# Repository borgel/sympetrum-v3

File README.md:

# What?
An electronic conference badge, of course! (That makes this a wearable right?)

If you're interested in keeping up to date with new versions, you can add your email here: 
https://goo.gl/forms/xGFPdRpdT4x1kmzG3 I'll send out (few) updates as I make progress towards whatever the next version is.

## Yes, but what does it do?
By default the device does pleasant RGB fades across its 48 RGB LEDs. It also sends a beacon in infrared every 30 seconds. They use any beacons received to synchronize a clock from which an animation is derived. The effect is that if one is alone, it plays random colors. If a group of them are together, they play the same rainbow water drop animation together.

For a little more information, last year's was [written up by Hackaday here](https://hackaday.com/2017/07/14/badge-from-diamond-age-comes-to-def-con/).

This is a partial rewrite of the work done for [DEFCON](https://defcon.org/) 25 ([here](https://github.com/borgel/sympetrum-v2)).

## Why is it a dragonfly?
If you haven't read Neal Stephenson's [_The Diamond Age: or, A Young Lady's Illustrated Primer_](http://www.goodreads.com/book/show/827.The_Diamond_Age), do that first. I'll wait.

If you have, there's a sequence around page 300 in which Miranda is first introduced to the possibility of using the drummers to find Nell. In this scene she attends a party in which the revellers wear colorful cloisonné dragonfly pins. As the party progresses they transition from random colorful flickering to some sort of synchrony, and Miranda notices the participants do the same. This is what I built.

A [_Sympetrum_](https://en.wikipedia.org/wiki/Sympetrum) is a genus of Dragonfly.

# Addons
Assembly instructions here: https://docs.google.com/document/d/1MZ-Gf56ivJ_pZaOBdA2XsJtWuKzQMPqqDXrGzq-pdRY/edit?usp=sharing

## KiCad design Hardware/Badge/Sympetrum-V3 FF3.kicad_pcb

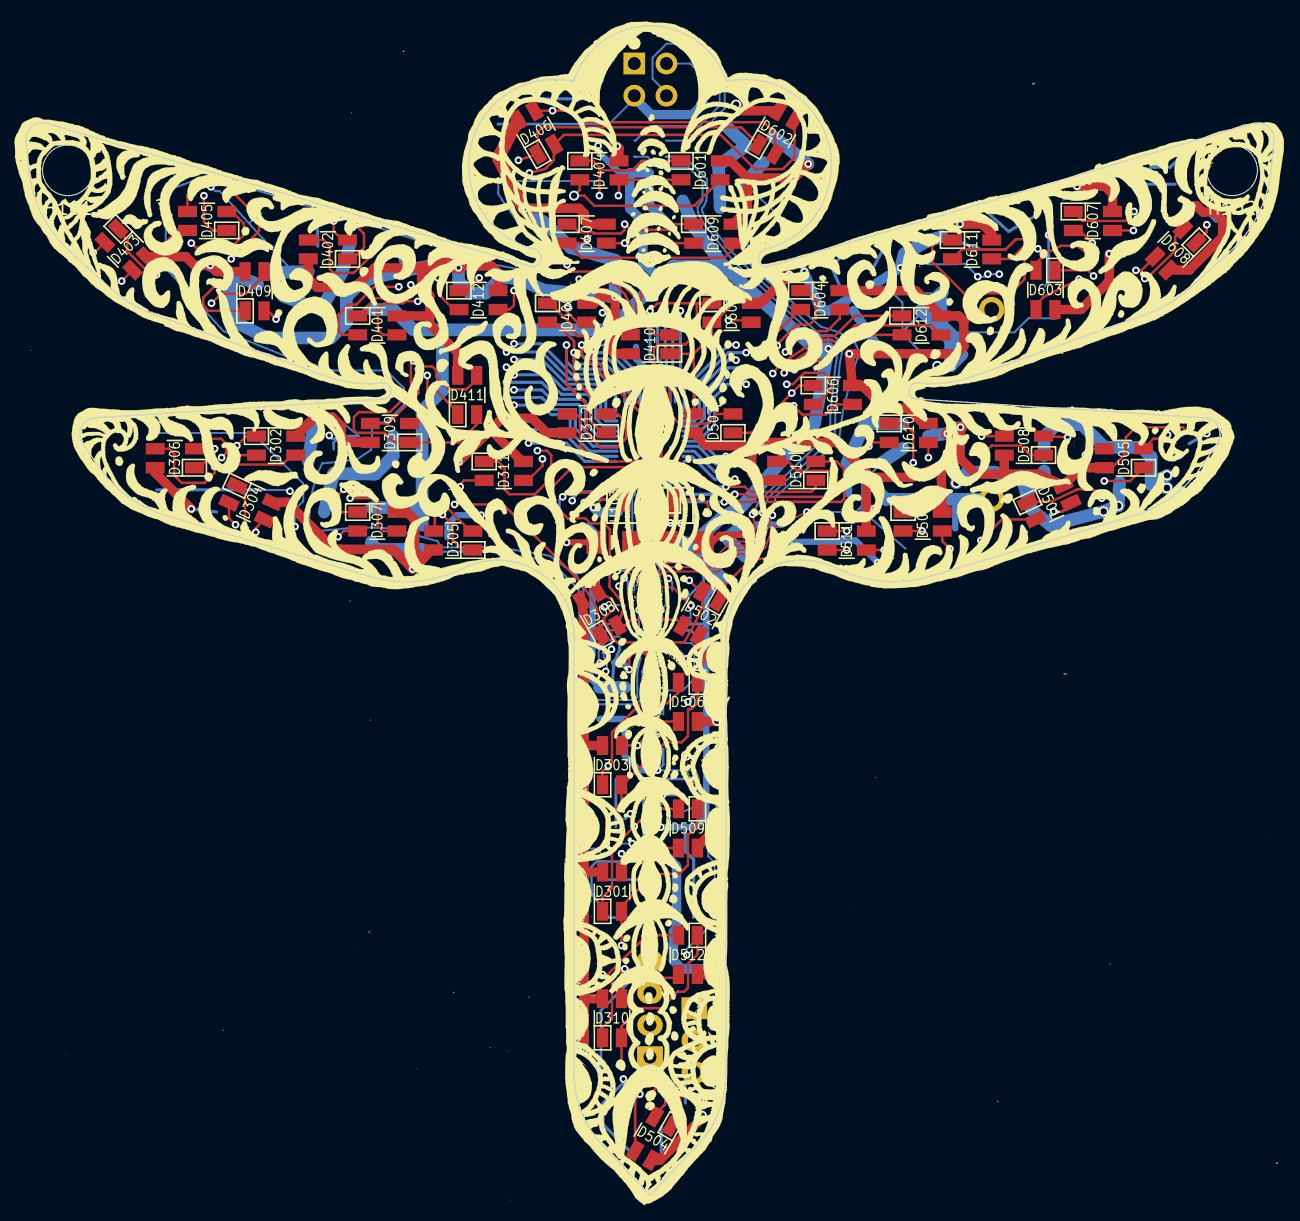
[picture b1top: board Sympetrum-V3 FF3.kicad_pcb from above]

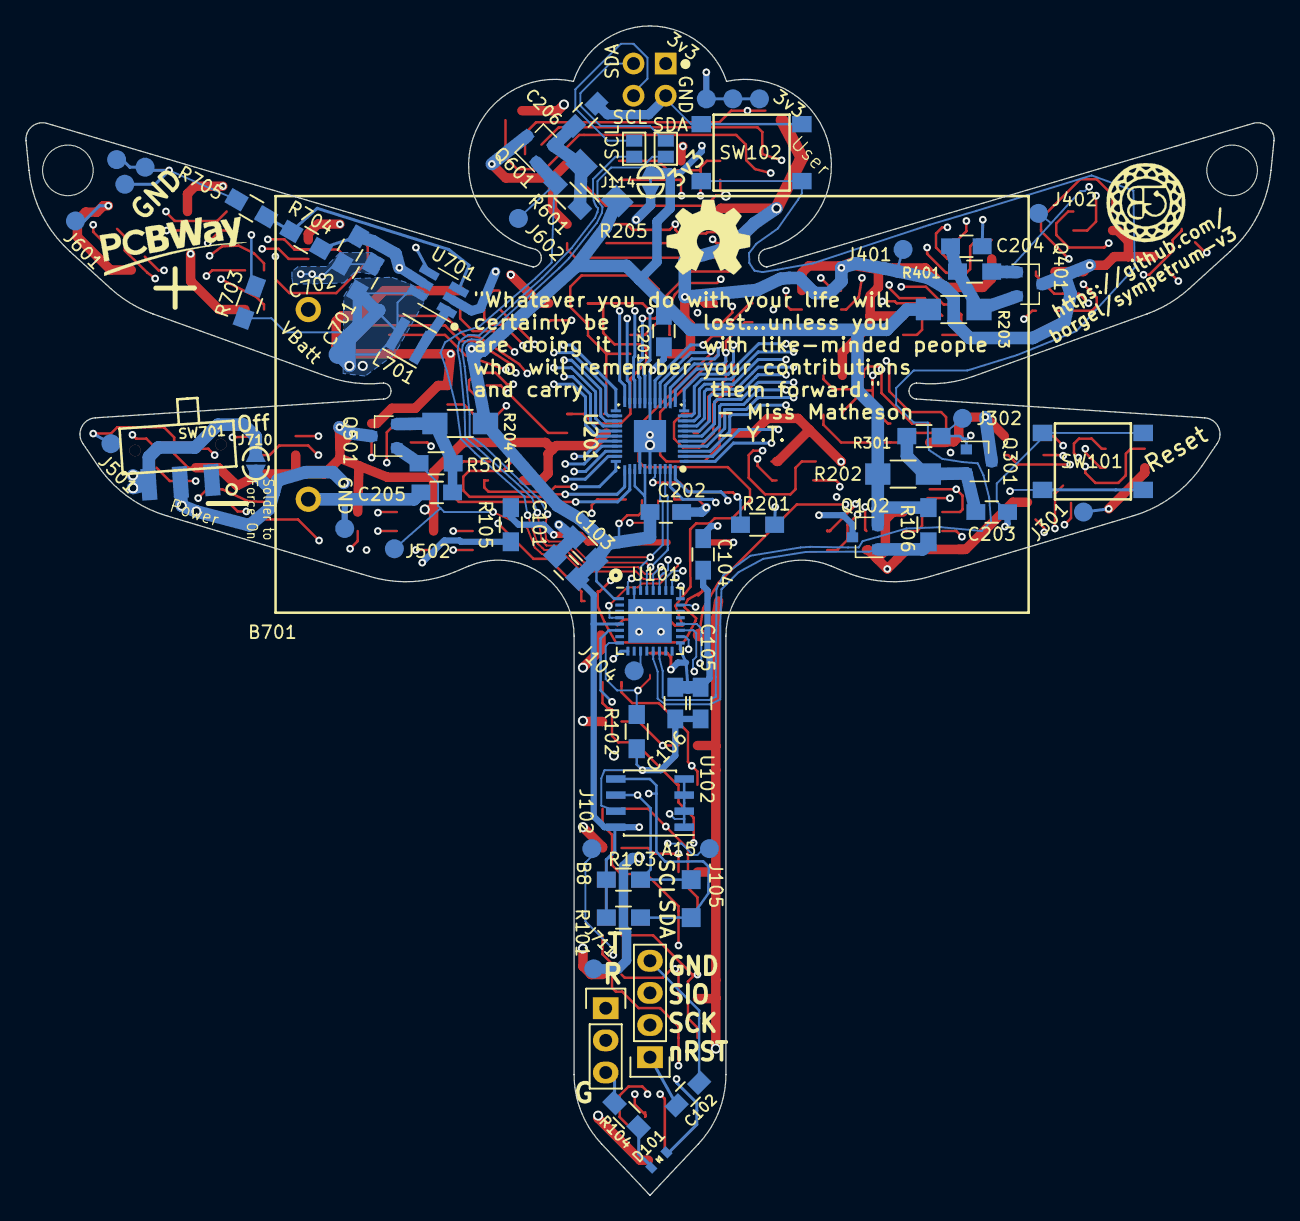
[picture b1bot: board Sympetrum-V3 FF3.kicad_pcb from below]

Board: 6 copper layers, 98.6 x 92.4 mm, 130 parts (75 on the bottom side), 78 nets.

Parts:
B701: Keystone_2462
C101, C102, C103: 100nF; C_0805_HandSoldering
C104, C701, C702: 4.7uF; C_0805_HandSoldering
C105, C201: 1uF; C_0805_HandSoldering
C106: 10nF; C_0805_HandSoldering
C202: 0.1uF; C_0805_HandSoldering
C203, C204, C205, C206: 22uF; C_0805_HandSoldering
D101: USR_LED-DNP; LED_0603_SmallSilk
D102, D103: IR25-21C/TR8; LED_1206_SmallSilk
D301, D302, D303, D304, D305, D306, D307, D308, D309, D310, D311, D312, D401, D402, D403, D404, D405, D406, D407, D408, D409, D410, D411, D412, D501, D502, D503, D504, D505, D506, D507, D508, D509, D510, D511, D512, D601, D602, D603, D604, D605, D606, D607, D608, D609, D610, D611, D612: SX-3528-RGB-ANODE; SX-3528-RGB-REORDERED-HiddenSilk
H101, H102: Hole-4mm-NPTH
J101: CONN_UART; Pin_Header_Straight_1x03
J102: B8; Measurement_Point_Round-SMD-Pad_Small
J104: A5; Measurement_Point_Round-SMD-Pad_Small
J105: A15; Measurement_Point_Round-SMD-Pad_Small
J107: TP_SDA; Measurement_Point_Square-SMD-Pad_Small
J108: CONN_SWD; Pin_Header_Straight_1x04
J109: TP_SCL; Measurement_Point_Square-SMD-Pad_Small
J110: 2x2-Shitty; 2x2_shitty
J111, J112: GS2
J114: GS2; SOLDER-JUMPER_1-WAY-SM-CLOSED
J301, J401, J501, J601: PWR; Measurement_Point_Round-SMD-Pad_Small
J302, J402, J502, J602: EN; Measurement_Point_Round-SMD-Pad_Small
J701, J702, J703, J708: GND; Measurement_Point_Round-SMD-Pad_Small
J704, J705, J706: 3v3; Measurement_Point_Round-SMD-Pad_Small
J709, J711: VBatt; Measurement_Point_Round-SMD-Pad_Small
J710: GS2; SOLDER-JUMPER_1-WAY-SM
L701: 4.7uH; Inductor_Taiyo-Yuden_MD-3030
Q101: ALS-PT19-315C/L177/TR8; LED_0603_SmallSilk
Q102, Q301, Q401, Q501, Q601: DMP3099L-7; SOT-23
R101, R103: 4.7k; R_0805_HandSoldering
R102: 3k; R_0805_HandSoldering
R104: 0R-DNP; R_0805_HandSoldering
R105: 47R; R_0805_HandSoldering
R106, R301, R401, R501, R601: 10k; R_0805_HandSoldering
R201: 5.6k; R_0805_HandSoldering
R202, R203, R204, R205: 0R; R_1206_HandSoldering
R703, R704: 1.02M; R_0805_HandSoldering
R705: 536K; R_0805_HandSoldering
SW101, SW102: C&K-PTS645SM43SMTR92-LFS; PTS645_SMT
SW701: JS102011SAQN; CK-JS102011SAQN_sm-spdt-switch
U101: STM32F051K8U6; QFN-32-1EP_5x5mm_Pitch0.5mm
U102: CAT24C512WI-GT3-DNP; SOIC-8_3.9x4.9mm_Pitch1.27mm
U103: TSOP75338WTT; TSOP753W
U201: IS31FL3236; QFN-44-5x5_Pitch0.4mm-Narrow
U701: AAT1217-1.2; SOT-23-6_Handsoldering

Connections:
+3V3: C101.1, C103.1, C104.1, C105.1, C106.1, C201.1, C202.1, C702.1, J114.1, J704.1, J705.1, J706.1, Q101.1, Q102.2, R101.1, R103.1, R106.1, R202.1, R203.1, R204.1, R205.1, R704.1, U101.1, U101.5, U101.17, U102.8, U103.2, U201.36, U201.38, U701.5
+BATT: B701.2, J710.2, SW701.3
/ADC_ALS: Q101.2, R102.1, U101.8
/DARKNET_IR_RX: U101.9, U103.3
/I2C1_SCL: J109.1, J112.2, R103.2, U101.29, U102.6, U201.42
/I2C1_SDA: J107.1, J111.2, R101.2, U101.30, U102.5, U201.41
/LED_ROW_1_CONTROL: J302.1, Q301.1, R301.2, U101.18
/LED_ROW_2_CONTROL: J402.1, Q401.1, R401.2, U101.26
/LED_ROW_3_CONTROL: J502.1, Q501.1, R501.2, U101.27
/LED_ROW_4_CONTROL: J602.1, Q601.1, R601.2, U101.28
/LEDs/12 RGB LEDs 2/Vin: C204.1, Q401.2, R203.2, R401.1
/LEDs/12 RGB LEDs 3/Vin: C205.1, Q501.2, R204.2, R501.1
/LEDs/12 RGB LEDs 4/Vin: C206.1, Q601.2, R205.2, R601.1
/LEDs/12 RGB LEDs/Vin: C203.1, Q301.2, R202.2, R301.1
/LEDs/LED1: D302.4, D403.3, D511.3, D603.2, U201.43
/LEDs/LED2: D302.2, D403.4, D511.2, D611.4, U201.44
/LEDs/LED3: D304.2, D405.2, D511.4, D607.2, U201.1
/LEDs/LED4: D304.4, D405.3, D503.2, D603.3, U201.2
/LEDs/LED5: D304.3, D405.4, D503.4, D607.4, U201.3
/LEDs/LED6: D305.4, D402.2, D503.3, D610.4, U201.4
/LEDs/LED7: D311.2, D402.4, D501.2, D610.3, U201.5
/LEDs/LED8: D308.4, D402.3, D502.4, D604.4, U201.6
/LEDs/LED9: D305.2, D401.2, D501.3, D610.2, U201.7
/LEDs/LED10: D305.3, D401.4, D501.4, D608.3, U201.8
/LEDs/LED11: D307.2, D401.3, D508.4, D603.4, U201.9
/LEDs/LED12: D307.3, D412.2, D508.3, D607.3, U201.10
/LEDs/LED13: D307.4, D412.4, D505.4, D606.3, U201.11
/LEDs/LED14: D312.2, D412.3, D505.3, D605.3, U201.12
/LEDs/LED15: D312.4, D408.2, D508.2, D608.2, U201.13
/LEDs/LED16: D312.3, D408.3, D505.2, D606.2, U201.14
/LEDs/LED17: D308.2, D410.2, D502.3, D611.2, U201.15
/LEDs/LED18: D308.3, D408.4, D502.2, D611.3, U201.16
/LEDs/LED19: D311.4, D410.3, D507.2, D605.4, U201.18
/LEDs/LED20: D311.3, D410.4, D507.3, D605.2, U201.19
/LEDs/LED21: D310.2, D406.2, D512.4, D602.3, U201.20
/LEDs/LED22: D310.4, D406.4, D512.2, D602.4, U201.21
/LEDs/LED23: D310.3, D406.3, D512.3, D602.2, U201.22
/LEDs/LED24: D303.4, D404.3, D506.2, D601.2, U201.23
/LEDs/LED25: D303.2, D404.4, D506.4, D601.4, U201.24
/LEDs/LED26: D301.2, D407.4, D509.4, D609.4, U201.25
/LEDs/LED27: D301.3, D407.3, D509.3, D609.2, U201.26
/LEDs/LED28: D303.3, D407.2, D506.3, D609.3, U201.27
/LEDs/LED29: D301.4, D404.2, D509.2, D601.3, U201.28
/LEDs/LED30: D306.3, D409.2, D504.2, D604.2, U201.29
/LEDs/LED31: D309.4, D411.2, D504.4, D604.3, U201.30
/LEDs/LED32: D309.2, D411.4, D504.3, D608.4, U201.31
/LEDs/LED33: D309.3, D411.3, D507.4, D606.4, U201.32
/LEDs/LED34: D306.2, D409.4, D510.4, D612.2, U201.33
/LEDs/LED35: D302.3, D409.3, D510.3, D612.3, U201.34
/LEDs/LED36: D306.4, D403.2, D510.2, D612.4, U201.35
/SWCLK: J108.2, U101.24
/SWDIO: J108.3, U101.23
/SYMP2_IR_TX: Q102.1, R106.2, U101.13
/USART1_MCU_RX: J101.2, U101.20
/USART1_MCU_TX: J101.1, U101.19
/USER_BUTTON: SW102.1, SW102.2, U101.14
/USER_LED: D101.2, U101.6
/nRST: C102.1, J108.1, SW101.3, SW101.4, U101.4
GND: B701.1, C101.2, C102.2, C103.2, C104.2, C105.2, C106.2, C201.2, C202.2, C203.2, C204.2, C205.2, C206.2, C701.2, C702.2, J101.3, J108.4, J110.2, J701.1, J702.1, J703.1, J708.1, R102.2, R104.1, R105.2, R201.2, R705.2, SW101.1, SW101.2, SW102.3, SW102.4, U101.31, U101.33, U102.1, U102.2, U102.3, U102.4, U102.7, U103.1, U103.4, U201.17, U201.37, U201.39, U701.2
unnamed: C701.1, J709.1, J710.1, J711.1, L701.1, R703.1, SW701.2, U701.6
unnamed: D101.1, R104.2
unnamed: D102.1, D103.2
unnamed: D102.2, Q102.3
unnamed: D103.1, R105.1
unnamed: D301.1, D302.1, D303.1, D304.1, D305.1, D306.1, D307.1, D308.1, D309.1, D310.1, D311.1, D312.1, J301.1, Q301.3
unnamed: D401.1, D402.1, D403.1, D404.1, D405.1, D406.1, D407.1, D408.1, D409.1, D410.1, D411.1, D412.1, J401.1, Q401.3
unnamed: D501.1, D502.1, D503.1, D504.1, D505.1, D506.1, D507.1, D508.1, D509.1, D510.1, D511.1, D512.1, J501.1, Q501.3
unnamed: D601.1, D602.1, D603.1, D604.1, D605.1, D606.1, D607.1, D608.1, D609.1, D610.1, D611.1, D612.1, J601.1, Q601.3
unnamed: J102.1, U101.32
unnamed: J104.1, U101.11
unnamed: J105.1, U101.25
unnamed: J110.1, J114.2
unnamed: J110.3, J111.1
unnamed: J110.4, J112.1
unnamed: L701.2, U701.1
unnamed: R201.1, U201.40
unnamed: R703.2, U701.4
unnamed: R704.2, R705.1, U701.3

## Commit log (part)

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2017-12-04 Add README and License
2017-12-04 Add ST CMSIS and HAL
2017-12-04 Improve gitignore
2017-12-04 Add test code
    Based on https://github.com/borgel/tomato-timer
2017-12-16 Move Firmware into a dir
2017-12-16 Add stub dirs for HW and Media
2017-12-16 Enable HAL TIM functions
2017-12-16 Fixup makefile
2017-12-16 SQME not working starting toi integrate symp-v2 IR
2017-12-23 Add reference IR files from sympetrum-v2
2017-12-23 Add DC Darknet IR sources
    Pulled from https://github.com/thedarknet/defcon25-badge
2017-12-23 Remove CPP cruft
2017-12-23 Rearrange my test code
2017-12-24 Get darknet to compile but not work
2017-12-24 Rip out all the sympetrum stuff and try to replace with darknet, it's all broken
2017-12-24 Remove added TIM16 init code
2017-12-24 Start integrating symp IR tech into darknet logic
2017-12-25 Progress towards IR send. Sending one bit!
2017-12-30 Maybe sending two bits? Closer anyway
2018-01-02 Remove most debug printing from IR TX pipe
2018-01-02 Add an init flag to IR so it can be safely restarted
2018-01-02 Confirmed background IR RX works! IR works!
2018-02-02 Start a simple LED test function
2018-02-02 Add basic matrix scan
2018-02-02 Start refactoring to look more like a real matrix fxn
2018-02-02 Pull in Sympetrum-V2 color utils
2018-02-02 Very rough first draft matrix driver
2018-02-03 Blank during matrix scan to avoid ghosting
2018-02-03 Cleanup matrix code a bit
2018-02-03 Add rainbow matrix demo
2018-02-03 Remove old channel control fxn
2018-02-03 Generate an 80Hz interrupt on TIM14
2018-02-03 Bump to 100Hz
2018-02-03 Make LED controller row writes also force a display update
2018-02-03 Split out an 'immediate force display refresh' fxn from what will be a state machine
2018-02-03 Disable blanking, turns out it doesn't matter if the display is mostly always on
2018-02-03 Turns out I don't need to spend time disabling rows during display either
2018-02-03 Reduce printing on LED init
2018-02-03 Factor matrix draw into a state machine and pump it from a timer at 100Hz
2018-02-03 Speed matrix timer up to 1kHz
2018-02-03 Add functions to stop and start matrix
2018-02-03 Cleanup dead code and comments
2018-02-03 More cleanup
2018-02-03 Remove old sympetrum IR code
2018-02-03 Start integrating reliable IR RX into main
2018-02-03 Return buffer length when dequeuing an incoming IR message
2018-02-03 More integration of RX into main loop
2018-02-05 Implicitely start/stop IR RX so it's more transparent to the user
2018-02-07 Decrease priority of matrix IRQ to allow IR to run at the same time
2018-02-07 Integrate matrix demo code with IR in main loop
2018-02-07 Improve IR pin macros
2018-02-07 Tweaks from review
2018-02-07 Normalize ir.c spacing
2018-02-07 Add test code for user button
2018-02-09 Add ADC drivers to the HAL
2018-02-09 Add (working!) first draft ADC code for ALS
2018-02-09 Tweak matrix pixel draw to take a pointer to a color
2018-02-09 Integrate crummy auto-dimming code with matrix demo
2018-02-09 Adjust matrix RGB test to do a simple color rotation
2018-03-15 Add stubs for test mode files
2018-03-15 Add pin defs for new TPs
2018-03-15 Check for and enter test mode on boot
2018-03-15 Progressively light R G and B of each display row
2018-03-15 Move user button to match FF1
2018-03-15 Assert power enable pin at boot
2018-03-15 Check if user button is idling properly
2018-03-15 Fix improperly called draw pixel
2018-03-15 Remap user button interrupt and handler
2018-03-15 Fix global R/G/B hue defines
2018-03-15 Broken checkpoint
2018-03-16 Disable IR RX while sending a buffer
2018-03-16 When starting and stopping IR RX check state
2018-03-16 Don't re-init IR when sending a test message in main
2018-03-16 Leave IR TX configured as PP for now
    OD seems to maybe not work.
2018-03-21 Add LED matrix commands to pause and resume it
2018-03-21 Adding/removing comments etc
2018-03-21 More cleanup of IR file
2018-03-21 Re-enable open drain mode for IR TX drive
    It works fine now that everything else is fixed.
2018-04-12 Add macros for A5 test point
2018-04-12 Add partial first pass IR test code
2018-04-14 Add an IR tests header to expose underlying functionality
2018-04-14 Rearrange entering test mode in main init
2018-04-14 Finish IR tests
    They seem to work?
2018-04-14 Add an LED test header to expose internal functions for tests
2018-04-14 Remove references to ALS test
2018-04-14 Fixes from review
2018-04-14 Add a tool to generate empty matrix mapping declarations
2018-04-14 Add a new file to hold the static mapping of physical channel to logical color
2018-04-14 Move LED channel and matrix info into platform_hw
2018-04-14 Start a stub script to generate the empty matrix map
2018-04-14 Begin mapping physical to logical LED channels
2018-04-15 WIP Added matrix mapping, not tested
2018-04-15 Added test code to light single LEDs
2018-04-16 WIP Mapping
2018-04-16 WIP I think the matrix map works for red now!?!
2018-04-16 Clean out debug code from matrix mapping tests
2018-04-16 Update test LED draw to use new matrix mapping
2018-04-25 Redefine raw matrix based on banks and channels
2018-04-25 WIP trying to fix mapping
2018-04-25 WIP linear version of lookup
2018-04-27 WIP rewriting matrix test draw
2018-04-27 WIP Fixed raw array indexing!
2018-04-28 Redo bank 1 mapping again to match layout
2018-04-28 WIP redo raw matrix array to be based on u8 channel not color struct
2018-04-29 Remove dead code in draw pixel fxns
2018-04-29 Add all LED bank mapping (tested working)
2018-04-29 Fix bank map spacing
2018-04-29 Clean up dead code
2018-04-29 Cleanup from review
2018-04-30 Remove unneeded LED channel macro
2018-04-30 Make user button interrupt on both edges
2018-04-30 Update user button handling to happen more in main
2018-04-30 Default LED global brightness to 100%
2018-04-30 WIP test order
2018-04-30 WIP broken IR stuff
2018-04-30 Track if system is in test mode and forward button presses to test module if so
2018-04-30 Be explicit about TP GPIO init
2018-04-30 Track if user button has been pressed in test mode
2018-04-30 Add the notion of a test plan, and run different tests on button press
2018-05-01 IR test code works!
2018-05-01 Fix IR TX GPIO configuration
    There is a pull up on board, but let's be absolutely sure.
2018-05-01 Add a fxn to set the value of a testpoint
2018-05-01 Add a function to get the value of a testpoint
2018-05-01 Make the first test plan item reset state
2018-05-01 Track the number of tests to run and number of completed cycles
2018-05-01 Remove old test failed fxn
2018-05-01 When toggling GPIO for matrix debug, use proper name macro
2018-05-01 Plumb GPIO interrupts on B8 into test module and handle them like a button
2018-05-01 Proper configure the TP GPIOs
2018-05-01 Add a handy wrapper for setting test fixture LEDs
2018-05-01 Track if test mode is active
2018-05-01 Track test passthrough flag better
2018-05-11 Start debugging test code with fixture
2018-05-11 Disable tests and old demo code
2018-05-11 WIP Start exploring chasing colors
2018-05-12 Break LED map init into a function
2018-05-12 Add a field to the LED mapping struct to store logical linear position
2018-05-12 Add drawing and mapping layers for logically linear addressing
2018-05-12 Add test code to do chasing LEDs, parallel top to bottom
2018-05-12 Add a blanking period to the matrix draw to remove flicker
2018-05-12 WIP start on sparse array
2018-05-12 Fill in sparse matrix with LED coordinates
2018-05-12 WIP sparse draw
2018-05-13 WIP Starting on polar addressing
2018-05-15 Finish adding polar addresses
2018-05-15 Add draw ring fxn and test code
2018-05-15 Try a COS table for LED fade
2018-05-17 Better button handling in main and move LED test patterns into a file
2018-05-17 Add a test mode for chasing around perimeter
2018-05-17 Add PDF reference for LED mapping
2018-05-17 Remove dead code from review
2018-05-17 Start files for pattern
2018-05-17 Add stubs for lighting control
2018-05-17 Rearrange ALS module to include hooks for starting and checking a reading
2018-05-17 Move IR init and monitoring into pattern
2018-05-17 Move ALS into lighting
2018-05-20 Convert ALS intensity into brightness buckets
2018-05-21 Pull in simple timer code from Tomato Timer v2
2018-05-21 Start a simple timer to track beacon intervals
2018-05-24 WIP Start adding very rough animation framework
2018-05-24 Run a coarse polar animation
2018-05-25 Pull in YABI submodule
2018-05-30 First pass initting YABI in lighting and using that for animation
2018-05-30 Pass a duration into YABI interpolated LED setting
2018-05-30 Add jitter parameter to LED channel set commands
2018-05-30 Cleanup comments
2018-05-30 Remove deprecated LED APIs
2018-05-30 Add CIE color correction LUT
2018-05-30 Add color API to CIE correct RGB colors
2018-05-30 CIE correct all LED drawing
2018-05-31 Add ability to travel up and down interaction ramp
2018-05-31 Pretend to send a beacon when user presses a the button
2018-06-02 Disable printing during IR send
2018-06-02 Add a TerribleTimer API to apply relative adjustment
2018-06-02 Add beacon module to manage sending and receiving IR beacons
2018-06-02 Make sure LED APIs are safe to call before pattern starts
2018-06-02 Send and receive beacons for real
2018-06-03 Adjust LED brightness fxn to take a global divisor
2018-06-03 Adjust LED brightness based on light level
2018-06-03 Fix ALS level type name
2018-06-03 Only apply ALS if it changes to avoid glitches
2018-06-03 When moving along the animation ramp, slew jitter
2018-06-03 Make internal IR fxns static
2018-06-03 Store animation period in the state struct
2018-06-03 Adjust numer of animation loops/ramp step to complete more full loops
2018-06-03 WIP send LED i2c with interrupts
2018-06-05 WIP try deferring i2c interrupt writes to main thread
2018-06-05 WIP got i2c to use interrupts but it's very broken
2018-06-05 Use a little state machine and fix descoping buffer problem with i2c IT
2018-06-06 Zero-init raw matrix buffer (so blanking row is 0d)
2018-06-09 Adjust math to prevent animation glitches
2018-06-09 Don't disable LEDs during IR TX
    Prevents glitching. Doesn't seem to effect IR reliability.
2018-06-09 Seed PRNG with board ID on boot
2018-06-09 Adjust beacon interval to 60s for faster clock sync
2018-06-10 LERP frame rate when changing it
2018-06-10 WIP fixing IR RX
2018-06-10 Temporarily switch to short beacon messages to improve reliablilty
2018-06-10 Set a flag if there was an RX error and reinit when we notice
2018-06-14 Update animation timer when slewing framerate, not jitter
2018-06-14 Make clock sync bump negative
2018-06-14 Speed up jitter ramp
2018-06-14 Change timer set API to take a flag to reset timer or not
2018-06-14 When sending a beacon, set jitter to 0 for a moment
    Looks like a send animation
2018-06-16 Switch then disable going to inverse jitter on beacon
2018-06-16 Change beacon interval to 30s
2018-06-19 On ramp, add a little timing jitter
2018-06-19 Change beacon length to a a full byte of ID
2018-06-19 Check only user button to enter tests on boot
2018-06-19 If test module says we should self test, do it
2018-06-19 Show IR test result on LED banks
2018-06-19 Bump version to 2
2018-06-19 Add v1 binaries
2018-06-23 Show IR test result on a different bank
    Don't want it to show up where the first LED test bank is.
2018-06-23 Reorder LED tests to start with blue
    So IR test results (red/green) can't be confused with LED tests.
2018-06-23 Show firmware version on LEDs at boot
2018-06-23 Remove dead code from main
2018-06-23 Add v2 release binaries to repo
2018-06-29 Add another parameter to the animation ramp to allow slower fades
2018-07-04 Set version LEDs so they are always dissimilar
2018-07-04 Be tollerant of a range of beacon lengths to allow adjustment in future
2018-07-04 Reset to recover the system if LED controller init fails
2018-07-04 Add v3 binaries
2018-07-04 Bump version to 4
2018-07-04 Make tests run themselves
2018-07-22 Display version for longer, try to do a full rainbow
2018-07-22 Add v4 release binaries
2018-07-23 Disregard any IR message formatting, accept all as beacons
2018-08-08 Add hardware sources
2018-08-08 Add a link to addon assembly instructions to README
2018-08-10 Add V5 binaries
